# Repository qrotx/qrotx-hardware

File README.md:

# qrotx Singleband Transmitter Hardware

This is work in progress, it has not yet been tested. Description and calculations will be added later.

## Cloning

This repository uses a git submodule for the KiCad symbol and footprint libraries. Clone with:

```bash
git clone --recurse-submodules git@github.com:qrotx/qrotx-singleband-hw.git
```

If you already cloned without `--recurse-submodules`, initialize the submodule with:

```bash
git submodule update --init
```

## Assembly

### NUCLEO-G474RE Board Modifications

The NUCLEO-G474RE board requires the following modifications before mounting on the PCB.
Reference: [UM2505 STM32G4 Nucleo-64 boards (MB1367) user manual](https://www.st.com/resource/en/user_manual/um2505-stm32g4-nucleo64-boards-mb1367-stmicroelectronics.pdf)

#### Power Supply (JP5)

Change jumper JP5 from the default **5V_STLK** position to the **E5V** position. This powers the
Nucleo board from the E5V pin supplied by the PCB instead of from USB.

#### HSE Clock — Oscillator from External PF0 (Section 7.5.1)

Modify the following solder bridges to configure the HSE clock input for an external
oscillator on PF0:

| Solder Bridge | Default | Required |
|---------------|---------|----------|
| SB24          | OFF     | OFF      |
| SB25          | ON      | OFF      |
| SB26          | ON      | OFF      |
| SB27          | OFF     | OFF      |
| SB28          | OFF     | ON       |

## License
These hardware designs are made available under the CERN Open Hardware Licence Version 2 - Strongly Reciprocal.
See [LICENSE](LICENSE) for the full text.

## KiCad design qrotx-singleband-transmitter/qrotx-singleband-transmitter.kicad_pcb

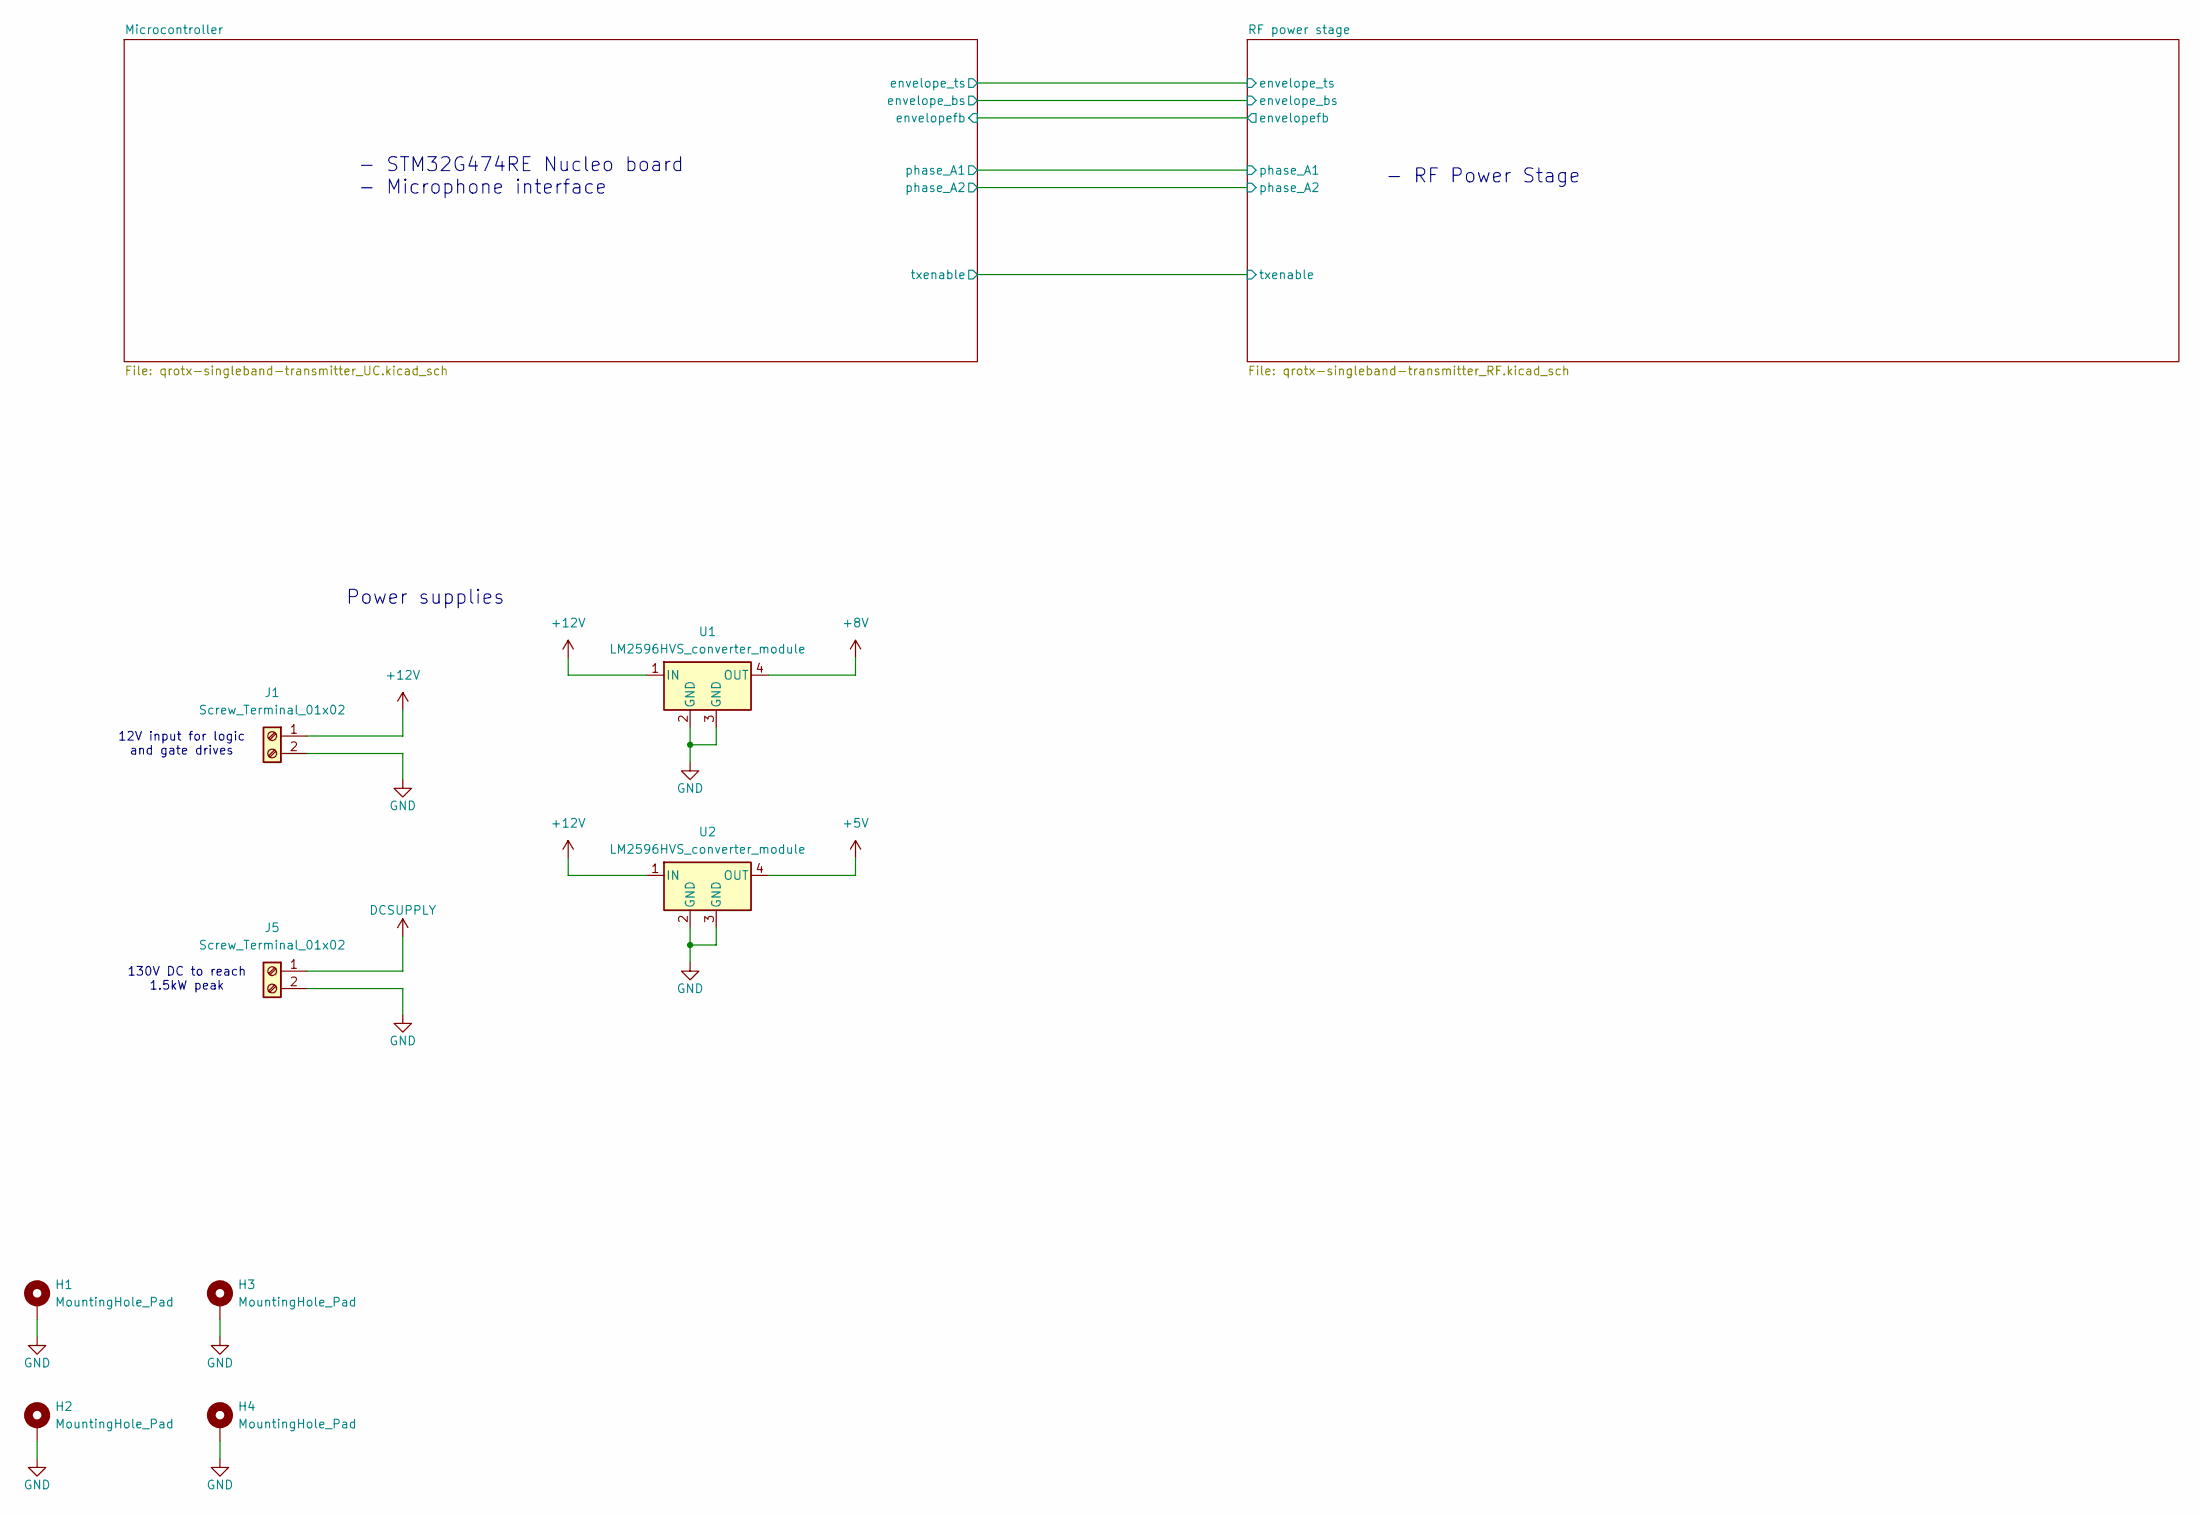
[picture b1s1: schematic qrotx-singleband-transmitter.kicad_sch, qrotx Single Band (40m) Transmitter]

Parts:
H1, H2, H3, H4: MountingHole_Pad; MountingHole_3.2mm_M3_Pad
J1, J5: Screw_Terminal_01x02; PhoenixContact_GMSTBV_2,5_2-GF-7,62_1x02_P7.62mm_Vertical_T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
U1, U2: LM2596HVS_converter_module; LM2596HVS module

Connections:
+5V: U2.4 (OUT); also elsewhere on the board
+8V: U1.4 (OUT); also elsewhere on the board
+12V: J1.1, U1.1 (IN), U2.1 (IN)
DCSUPPLY: J5.1; also elsewhere on the board
GND: H1.1, H2.1, H3.1, H4.1, J1.2, J5.2, U1.2 (GND), U1.3 (GND), U2.2 (GND), U2.3 (GND); also elsewhere on the board

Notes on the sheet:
Power supplies
130V DC to reach 1.5kW peak
- STM32G474RE Nucleo board - Microphone interface
12V input for logic and gate drives
- RF Power Stage

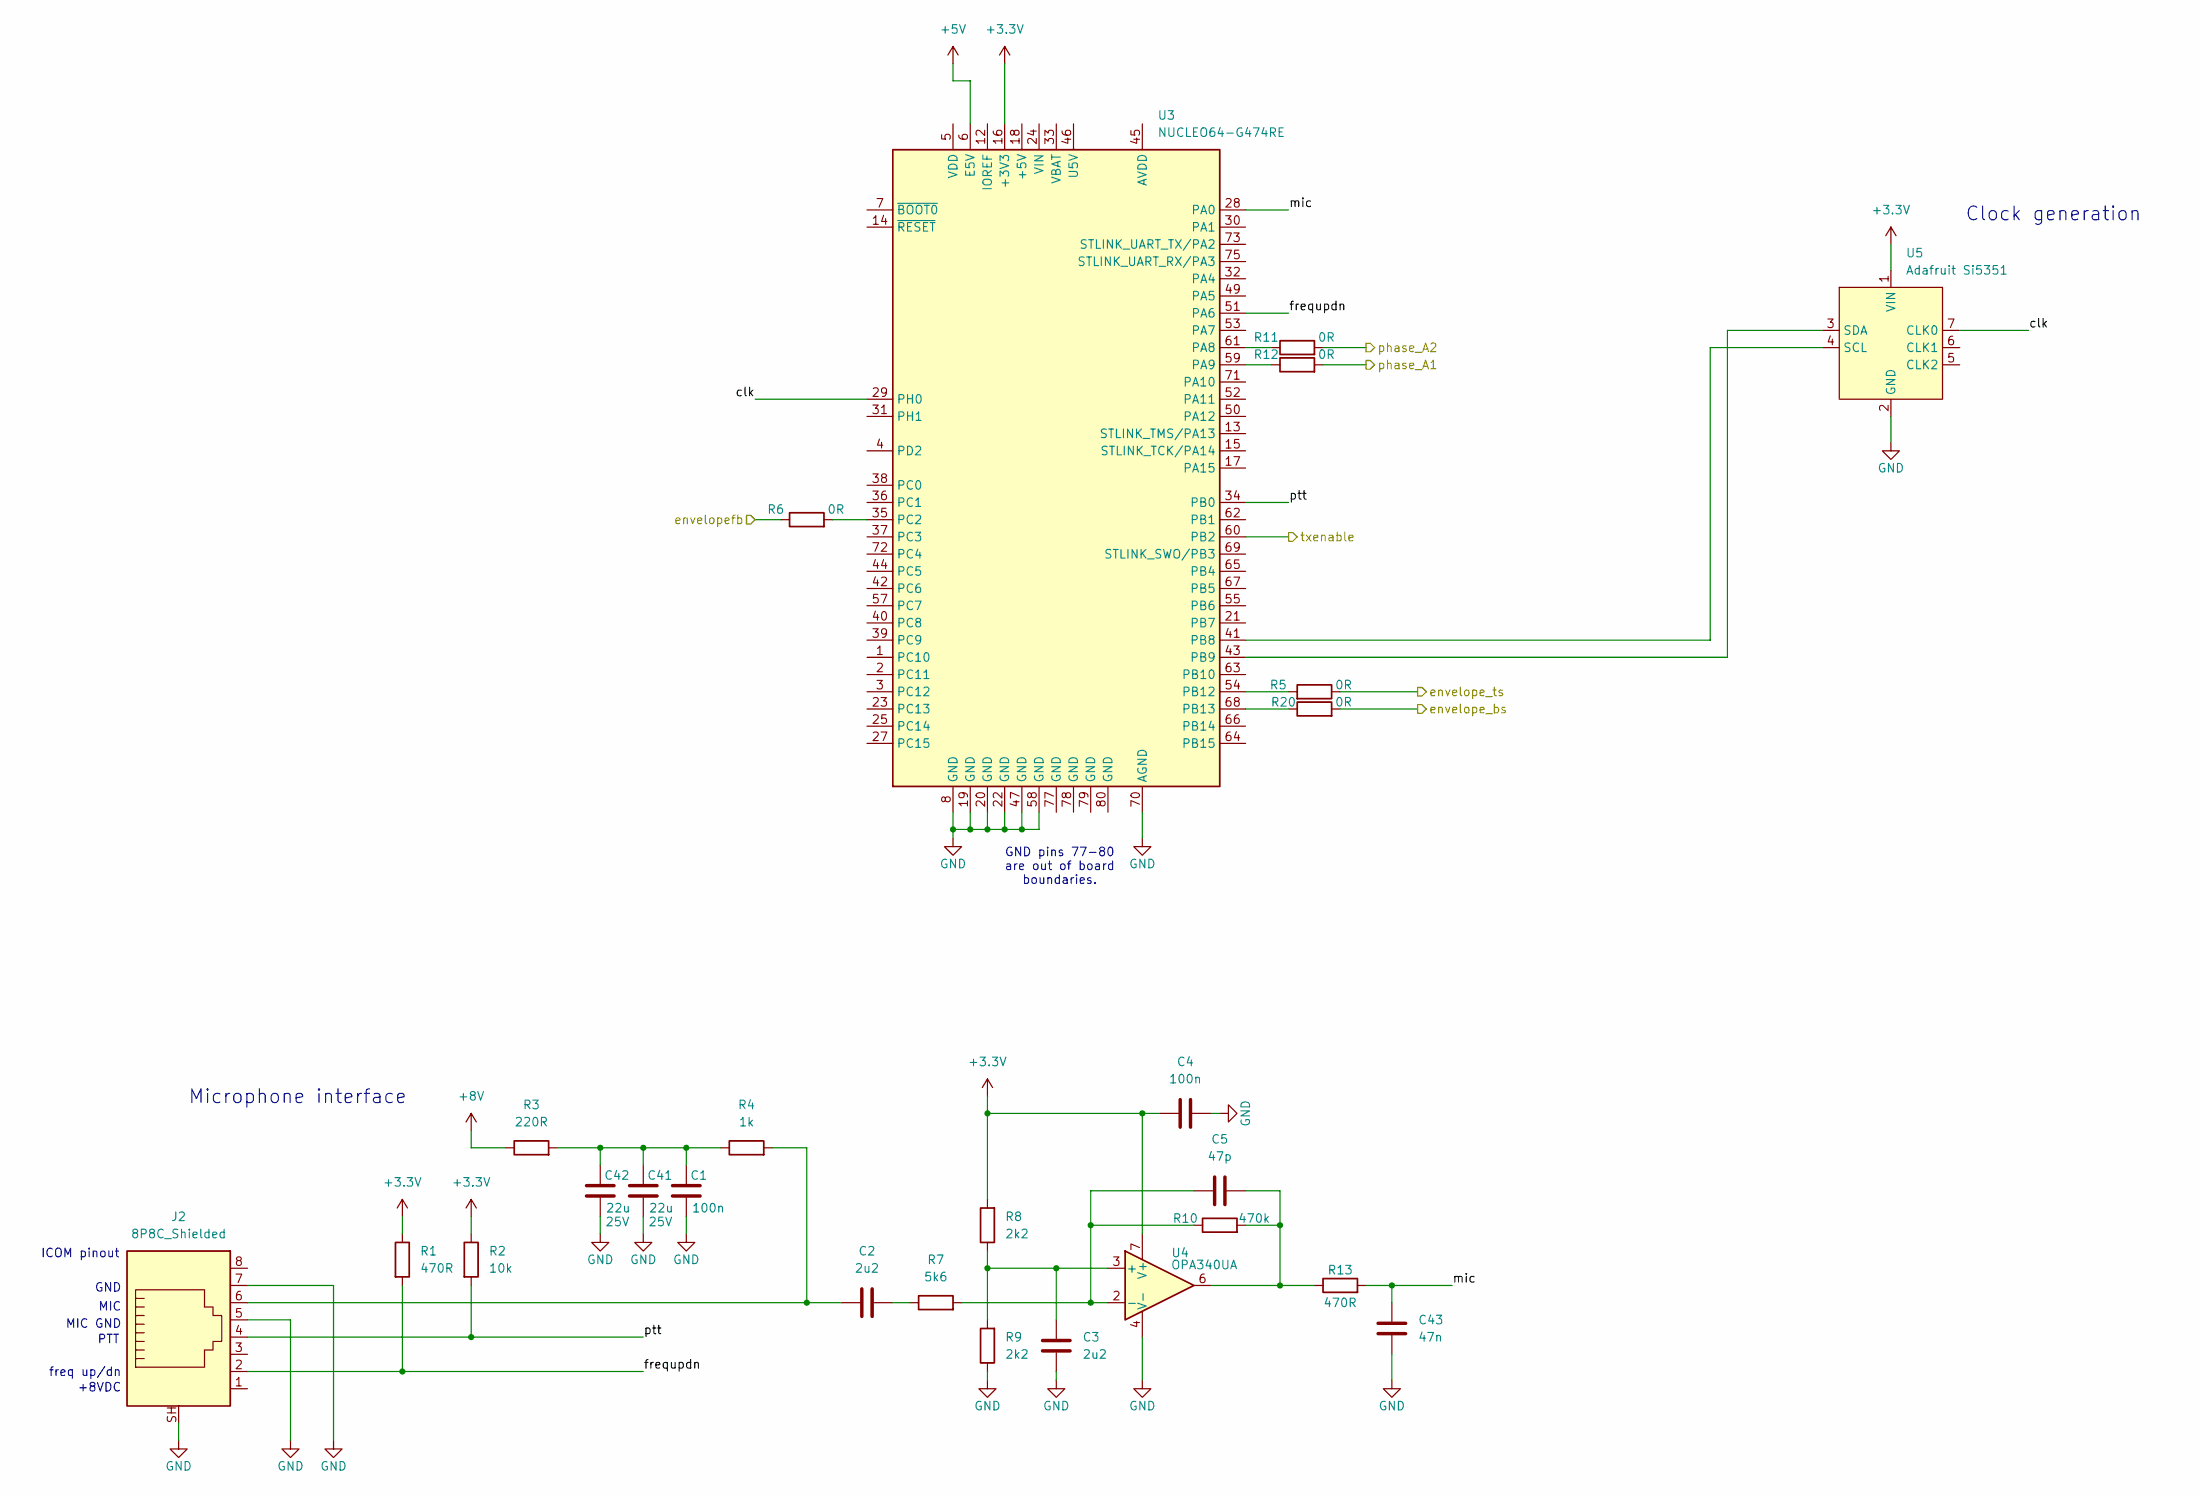
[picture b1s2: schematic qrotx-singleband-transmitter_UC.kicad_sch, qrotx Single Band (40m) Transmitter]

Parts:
C1, C4: 100n; C_0603_1608Metric
C2, C3: 2u2; C_0603_1608Metric
C5: 47p; C_0603_1608Metric
C41, C42: 22u; C_1210_3225Metric; Voltage 25V
C43: 47n; C_0603_1608Metric
J2: 8P8C_Shielded; RJ45_Amphenol_RJHSE5380
R1, R13: 470R; R_0603_1608Metric
R2: 10k; R_0603_1608Metric
R3: 220R; R_0603_1608Metric
R4: 1k; R_0603_1608Metric
R5, R6, R11, R12, R20: 0R; R_0603_1608Metric
R7: 5k6; R_0603_1608Metric
R8, R9: 2k2; R_0603_1608Metric
R10: 470k; R_0603_1608Metric
U3: NUCLEO64-G474RE; ST_Morpho_Connector_64_STLink
U4: OPA340UA; SOIC-8_3.9x4.9mm_P1.27mm
U5: Adafruit Si5351; Adafruit_Si5351

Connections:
+3.3V: C4.1, R1.1, R2.1, R8.2, U3.16 (+3V3), U4.7 (V+), U5.1 (VIN)
+5V: U3.6 (E5V); also elsewhere on the board
+8V: R3.1; also elsewhere on the board
/Microcontroller/clk: U3.29 (PH0), U5.7 (CLK0)
/Microcontroller/envelope_bs: R20.2; also elsewhere on the board
/Microcontroller/envelope_ts: R5.1; also elsewhere on the board
/Microcontroller/envelopefb: R6.1; also elsewhere on the board
/Microcontroller/frequpdn: J2.2, R1.2, U3.51 (PA6)
/Microcontroller/mic: C43.1, R13.2, U3.28 (PA0)
/Microcontroller/phase_A1: R12.2; also elsewhere on the board
/Microcontroller/phase_A2: R11.2; also elsewhere on the board
/Microcontroller/ptt: J2.4, R2.2, U3.34 (PB0)
/Microcontroller/txenable: U3.60 (PB2); also elsewhere on the board
GND: C1.2, C3.2, C4.2, C41.2, C42.2, C43.2, J2.5, J2.7, J2.SH, R9.1, U3.8 (GND), U3.19 (GND), U3.20 (GND), U3.22 (GND), U3.47 (GND), U3.58 (GND), U3.70 (AGND), U4.4 (V-), U5.2 (GND); also elsewhere on the board
unnamed: C1.1, C41.1, C42.1, R3.2, R4.1
unnamed: C2.1, J2.6, R4.2
unnamed: C2.2, R7.1
unnamed: C5.2, R10.2, R13.1, U4.6
unnamed: R11.1, U3.61 (PA8)
unnamed: R12.1, U3.59 (PA9)
unnamed: U3.41 (PB8), U5.4 (SCL)
unnamed: U3.43 (PB9), U5.3 (SDA)
unnamed: R5.2, U3.54 (PB12)
unnamed: R20.1, U3.68 (PB13)
unnamed: R6.2, U3.35 (PC2)
unnamed: C3.1, R8.1, R9.2, U4.3 (+)
unnamed: C5.1, R7.2, R10.1, U4.2 (-)

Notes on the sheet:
freq up/dn
ICOM pinout
GND
MIC
Clock generation
GND pins 77-80 are out of board boundaries.
+8VDC
PTT
Microphone interface
MIC GND

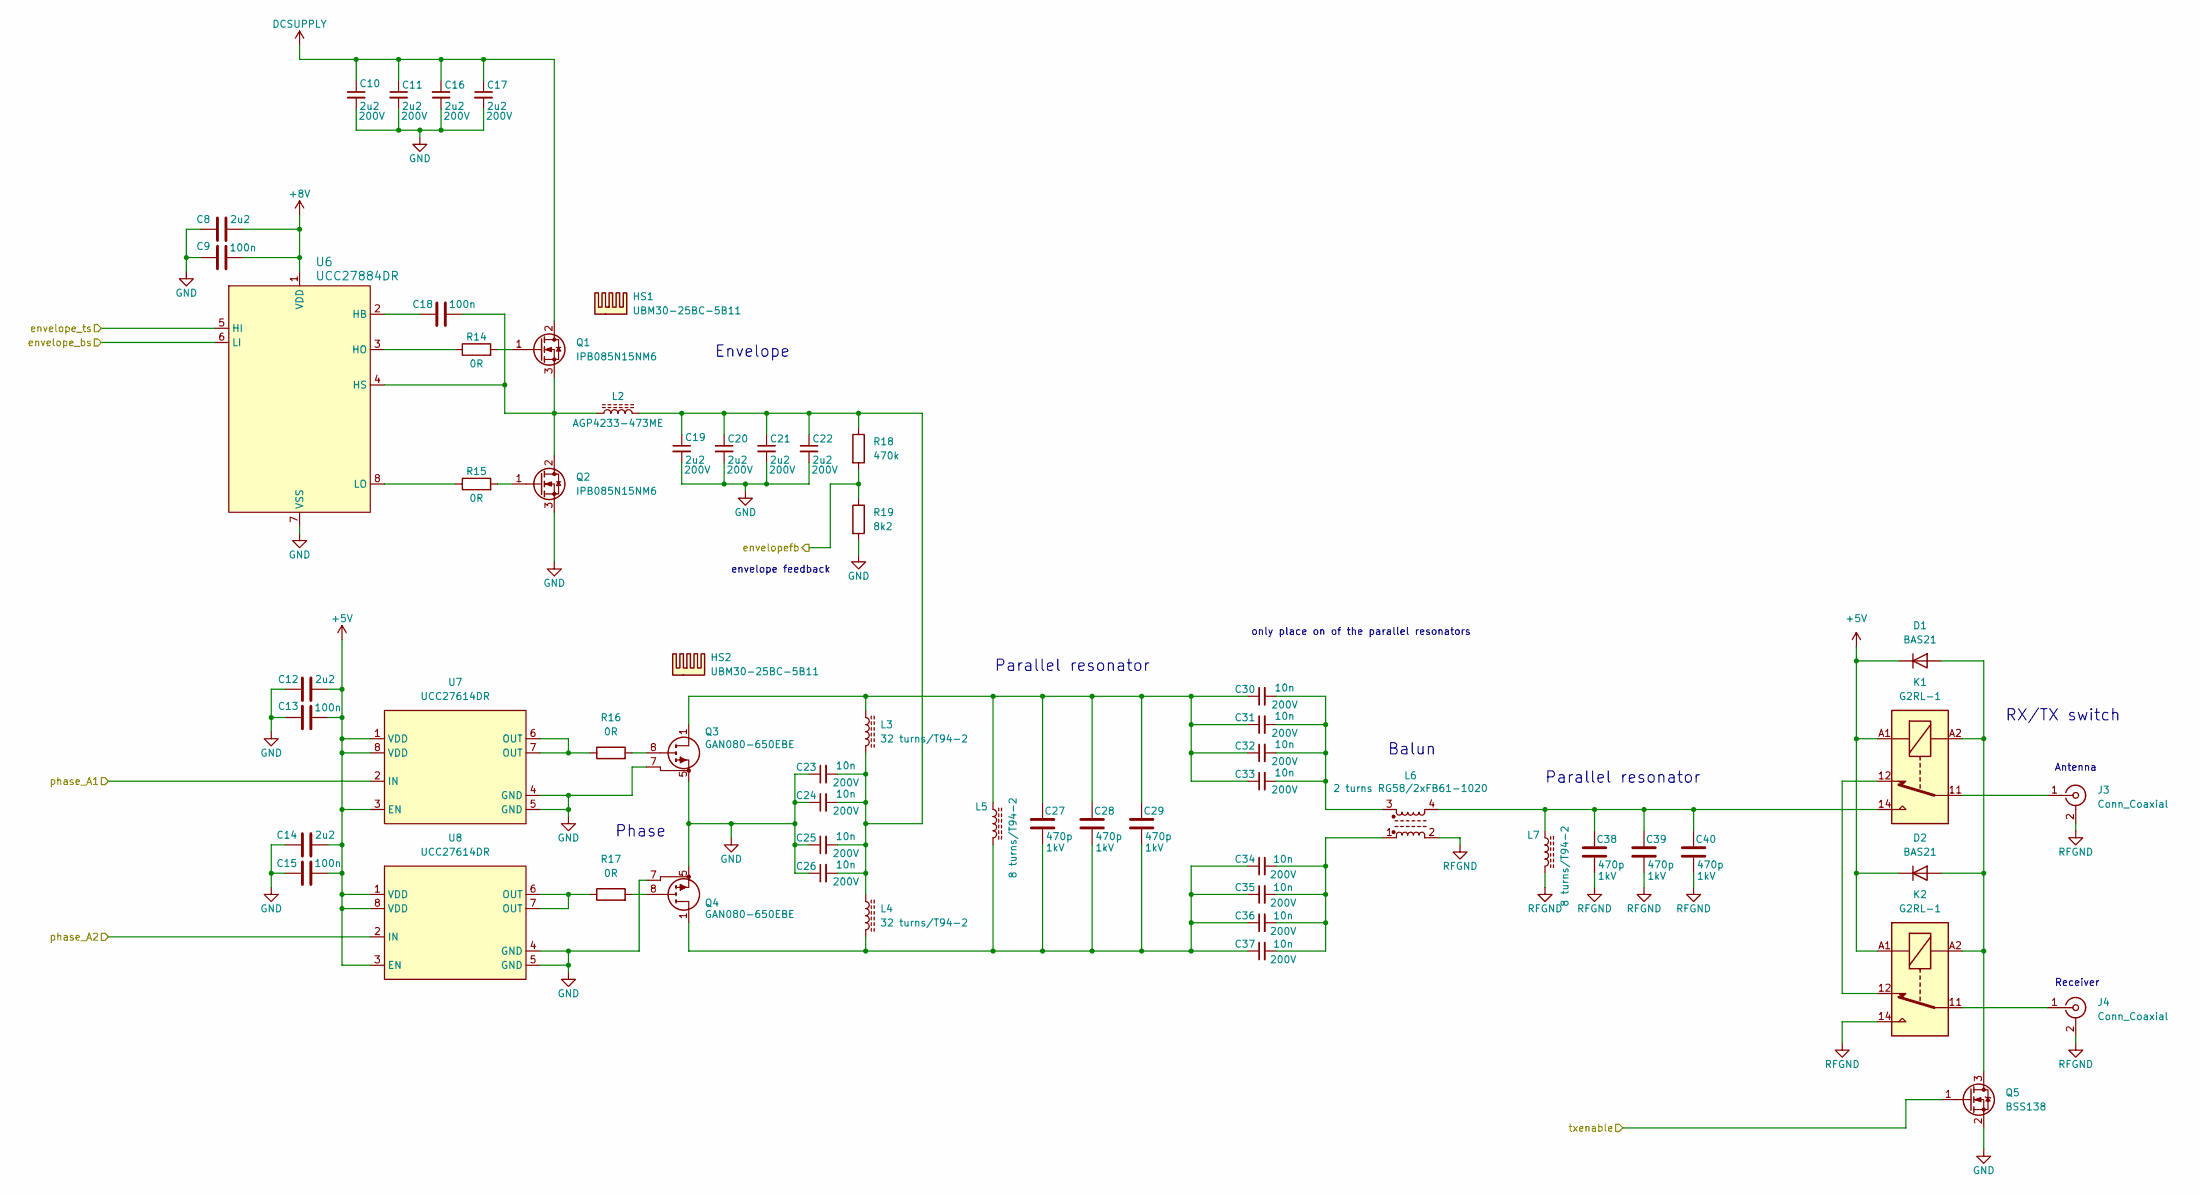
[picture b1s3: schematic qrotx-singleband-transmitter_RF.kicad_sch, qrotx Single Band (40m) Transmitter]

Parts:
C8, C12, C14: 2u2; C_0603_1608Metric
C9, C13, C15, C18: 100n; C_0603_1608Metric
C10, C11, C16, C17, C19, C20, C21, C22: 2u2; C_2220_5750Metric; Voltage 200V
C23, C24, C25, C26, C30, C31, C32, C33, C34, C35, C36, C37: 10n; C_1206_3216Metric; Voltage 200V
C27, C28, C29, C38, C39, C40: 470p; C_1206_3216Metric; Voltage 1kV
D1, D2: BAS21; SOT-23
HS1, HS2: UBM30-25BC-5B11; Heatsink_Alpha_UBM30-xxBP
J3: Conn_Coaxial; RF_output_pins
J4: Conn_Coaxial; SMA_Amphenol_901-144_Vertical
K1, K2: G2RL-1; Relay_SPDT_Omron_G2RL-1
L2: AGP4233-473ME; AGP4233-682-154
L3, L4: 32 turns/T94-2; t94-2_inductor_narrow
L5, L7: 8 turns/T94-2; t94-2_inductor
L6: 2 turns RG58/2xFB61-1020; tline_balun_pads
Q1, Q2: IPB085N15NM6; TO-263-2_ThermalVias
Q3, Q4: GAN080-650EBE; DFN8080-8_ThermalVias
Q5: BSS138; SOT-23
R14, R15, R16, R17: 0R; R_0603_1608Metric
R18: 470k; R_0603_1608Metric
R19: 8k2; R_0603_1608Metric
U6: UCC27884DR; SOIC-8_3.9x4.9mm_P1.27mm
U7, U8: UCC27614DR; SOIC-8_3.9x4.9mm_P1.27mm

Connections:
+5V: C12.2, C13.2, C14.2, C15.2, D1.3 (K), D2.3 (K), K1.A1, K2.A1, U7.1 (VDD), U7.3 (EN), U7.8 (VDD), U8.1 (VDD), U8.3 (EN), U8.8 (VDD); also elsewhere on the board
+8V: C8.2, C9.2, U6.1 (VDD); also elsewhere on the board
/Microcontroller/envelope_bs: U6.6 (LI); also elsewhere on the board
/Microcontroller/envelope_ts: U6.5 (HI); also elsewhere on the board
/Microcontroller/envelopefb: R18.2, R19.1; also elsewhere on the board
/Microcontroller/phase_A1: U7.2 (IN); also elsewhere on the board
/Microcontroller/phase_A2: U8.2 (IN); also elsewhere on the board
/Microcontroller/txenable: Q5.1 (G); also elsewhere on the board
DCSUPPLY: C10.1, C11.1, C16.1, C17.1, Q1.2 (D); also elsewhere on the board
GND: C8.1, C9.1, C10.2, C11.2, C12.1, C13.1, C14.1, C15.1, C16.2, C17.2, C19.2, C20.2, C21.2, C22.2, C23.1, C24.1, C25.1, C26.1, Q2.3 (S), Q3.5 (S), Q3.6 (S), Q3.7 (SS), Q3.9 (S), Q4.5 (S), Q4.6 (S), Q4.7 (SS), Q4.9 (S), Q5.2 (S), R19.2, U6.7 (VSS), U7.4 (GND), U7.5 (GND), U8.4 (GND), U8.5 (GND); also elsewhere on the board
unnamed: C19.1, C20.1, C21.1, C22.1, C23.2, C24.2, C25.2, C26.2, L2.2, L3.2, L4.1, R18.1
unnamed: C27.1, C28.1, C29.1, C30.1, C31.1, C32.1, C33.1, L3.1, L5.1, Q3.1 (D), Q3.2 (D), Q3.3 (D), Q3.4 (D)
unnamed: C27.2, C28.2, C29.2, C34.1, C35.1, C36.1, C37.1, L4.2, L5.2, Q4.1 (D), Q4.2 (D), Q4.3 (D), Q4.4 (D)
unnamed: C30.2, C31.2, C32.2, C33.2, L6.3
unnamed: C34.2, C35.2, C36.2, C37.2, L6.1
unnamed: C38.1, C39.1, C40.1, K1.14, L6.4, L7.1
unnamed: D1.1 (A), D2.1 (A), K1.A2, K2.A2, Q5.3 (D)
unnamed: J3.1 (In), K1.11
unnamed: J4.1 (In), K2.11
unnamed: K1.12, K2.12
unnamed: Q1.1 (G), R14.2
unnamed: C18.2, L2.1, Q1.3 (S), Q2.2 (D), U6.4 (HS)
unnamed: Q2.1 (G), R15.2
unnamed: Q3.8 (G), R16.2
unnamed: Q4.8 (G), R17.2
unnamed: R16.1, U7.6 (OUT), U7.7 (OUT)
unnamed: R17.1, U8.6 (OUT), U8.7 (OUT)
unnamed: C18.1, U6.2 (HB)
unnamed: R14.1, U6.3 (HO)
unnamed: R15.1, U6.8 (LO)
RFGND: C38.2, C39.2, C40.2, J3.2 (Ext), J4.2 (Ext), K2.14, L6.2, L7.2

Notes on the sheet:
Balun
Parallel resonator
Phase
only place on of the parallel resonators
envelope feedback
RX/TX switch
Envelope
Receiver
Antenna

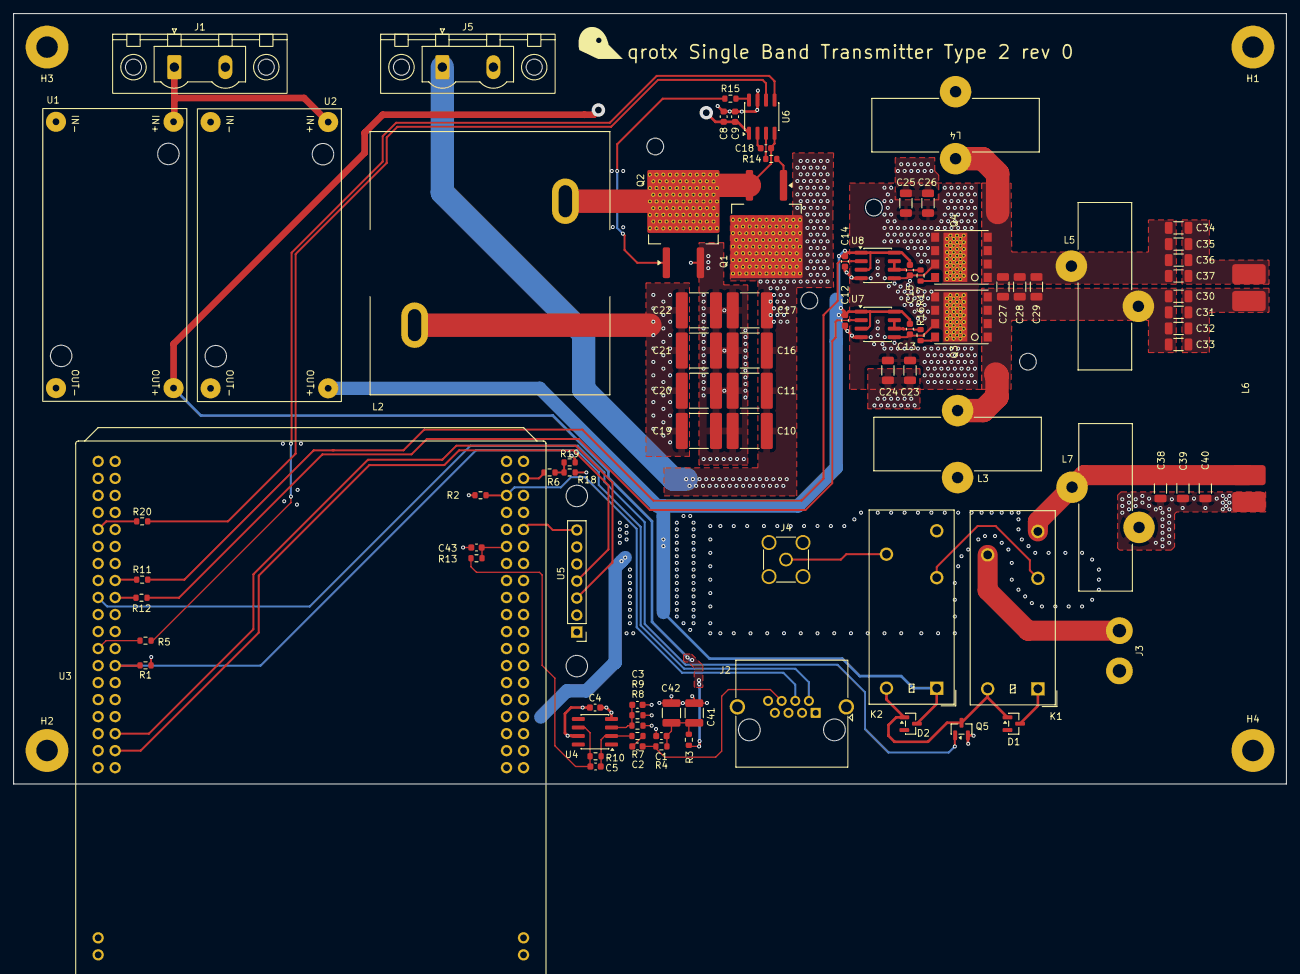
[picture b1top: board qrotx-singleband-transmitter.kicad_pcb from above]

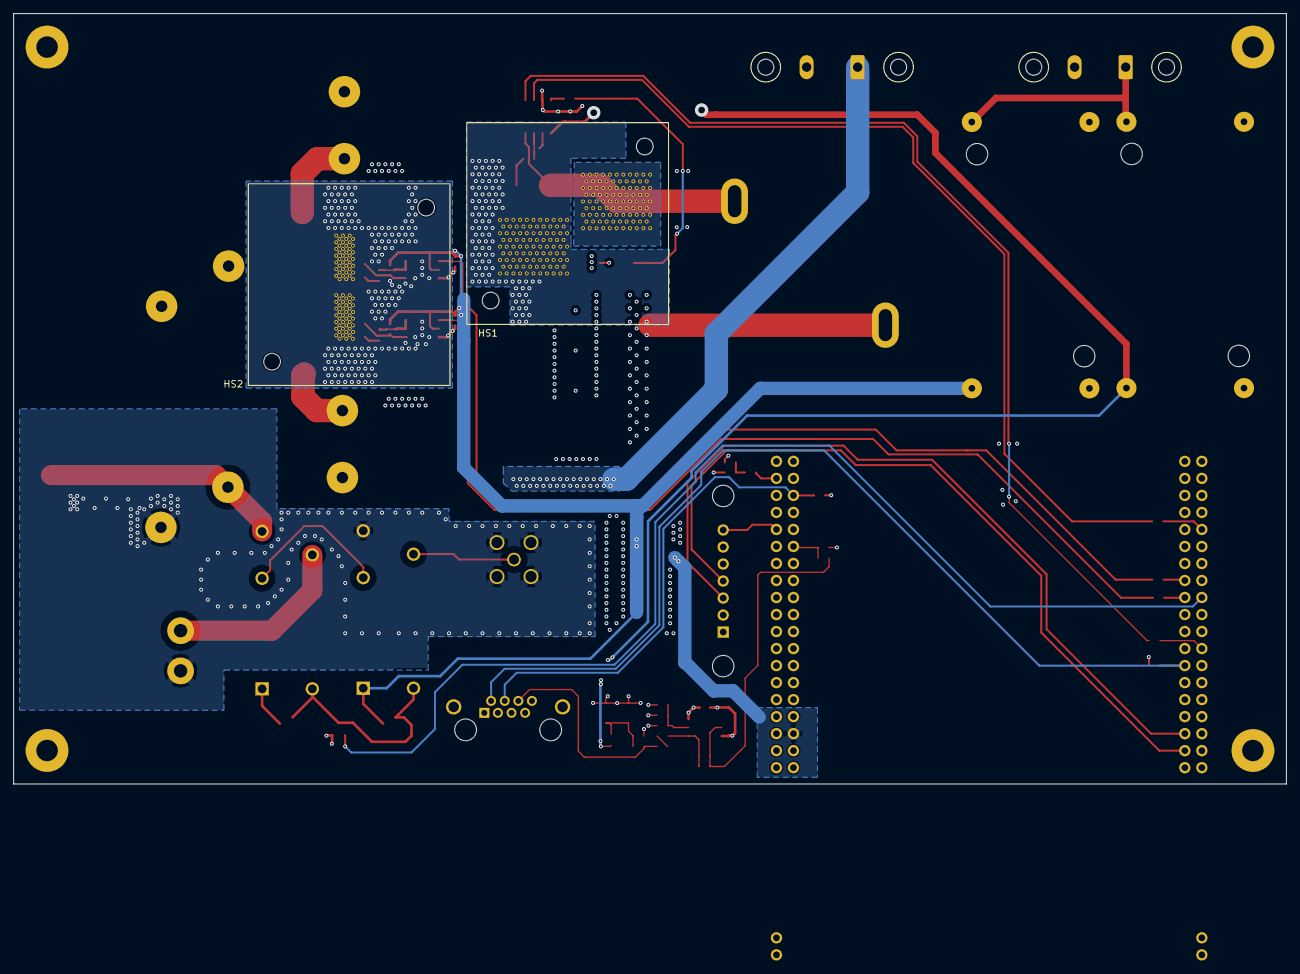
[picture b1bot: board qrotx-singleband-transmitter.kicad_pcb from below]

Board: 4 copper layers, 190.0 x 115.0 mm, 95 parts (2 on the bottom side), 50 nets.

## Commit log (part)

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2026-04-07 Initial design of the single band transmitter
2026-04-07 Update text blocks in drawings
2026-04-07 Add Kicad jobset to generate output and commit pdf
2026-04-07 gitignore .lck files
2026-04-10 Create README.md for qrotx hardware project
2026-04-16 Add pick and place file generation to jobset
2026-05-05 Add .claude directory to .gitignore
2026-05-05 Update components submodule

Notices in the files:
qrotx-singleband-transmitter/qrotx-singleband-transmitter.kicad_pcb:
Copyright (c) 2024-2026 Christian Riesch, christian@riesch.at
Licensed under CERN-OHL-S v2 or any later version, https://ohwr.org/cern_ohl_s_v2.txt
